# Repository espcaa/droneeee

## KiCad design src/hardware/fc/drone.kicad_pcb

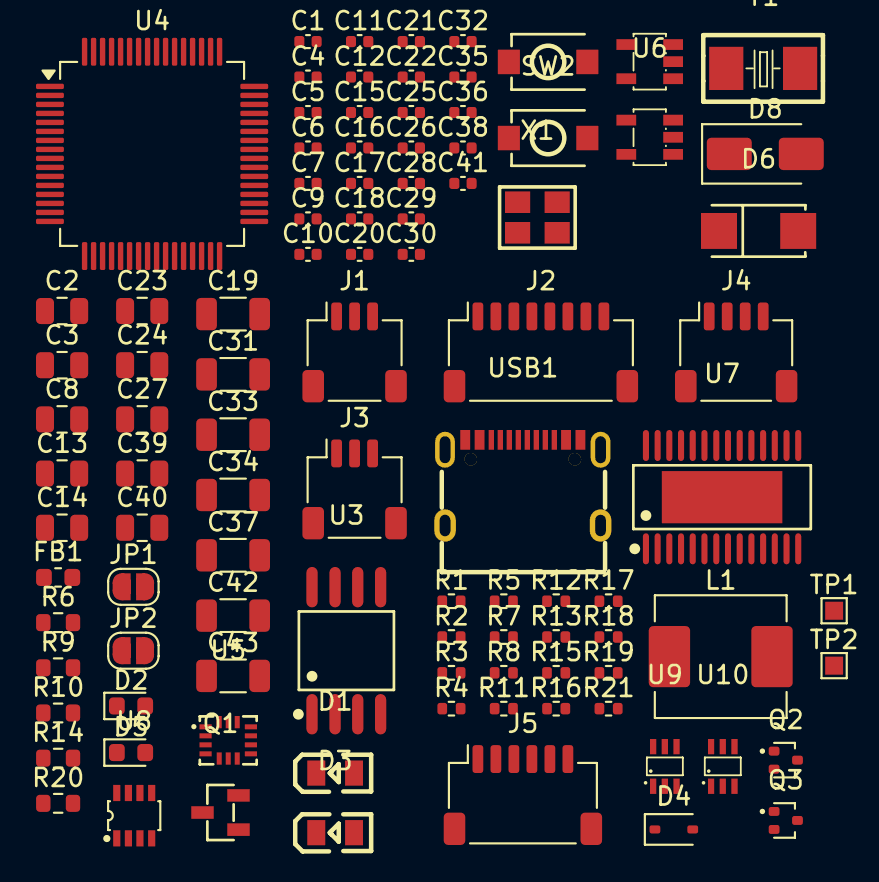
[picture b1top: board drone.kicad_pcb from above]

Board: 2 copper layers, 99 parts (0 on the bottom side), 73 nets, no tracks yet.

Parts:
C1, C4, C5, C6, C7, C11, C12, C15, C16, C17, C18, C20, C21, C22, C25, C26, C28, C29, C30, C32, C38, C41: 100nf; C_0402_1005Metric
C2, C3, C27: 2.2uf; C_0805_2012Metric
C8, C13, C14, C23, C24, C39, C40: 1uf; C_0805_2012Metric
C9, C10: 22pf; C_0402_1005Metric
C19, C31, C33, C34, C37, C42, C43: 22uf; C_1206_3216Metric
C35, C36: 33pf; C_0402_1005Metric
D1: C2297; LED0805-R-RD
D2, D5: LED; LED_0603_1608Metric
D3: C2296; LED0805-R-RD
D4: D_Schottky; D_SOD-323
D6: D_Schottky; SMA_L4.3-W2.6-LS5.2-RD
D8: SMAJ30A; D_SMA
FB1: FerriteBead; L_0603_1608Metric
J1, J3: Conn_01x03; JST_SH_SM03B-SRSS-TB_1x03-1MP_P1.00mm_Horizontal
J2: Conn_01x08; JST_SH_SM08B-SRSS-TB_1x08-1MP_P1.00mm_Horizontal
J4: Conn_01x04; JST_SH_SM04B-SRSS-TB_1x04-1MP_P1.00mm_Horizontal
J5: Conn_01x06; JST_SH_SM06B-SRSS-TB_1x06-1MP_P1.00mm_Horizontal
JP1, JP2: Jumper_2_Open; SolderJumper-2_P1.3mm_Open_RoundedPad1.0x1.5mm
L1: 1OuH; L_KOHERelec_MDA7030
Q1: AO3400A; SOT-23-3_L2.9-W1.3-P1.90-LS2.4-BR
Q2, Q3: NPN; SOT-416
R1, R2, R3, R4, R13, R17: 10k; R_0402_1005Metric
R5: 20; R_0402_1005Metric
R6: 7.68k; R_0603_1608Metric
R7: 51k; R_0402_1005Metric
R8: 41.2k; R_0402_1005Metric
R9: 1k; R_0603_1608Metric
R10, R14: 75; R_0603_1608Metric
R11, R18, R19, R21: 1k; R_0402_1005Metric
R12: 100k; R_0402_1005Metric
R15, R16: 5.1k; R_0402_1005Metric
R20: 150k; R_0603_1608Metric
SW1, SW2: SW_Push; SW-SMD_L3.9-W3.0-P4.45
TP1: BUZZER+; TestPoint_Pad_1.0x1.0mm
TP2: BUZZER-; TestPoint_Pad_1.0x1.0mm
U2: TLV75533PDBVR; SOT-23-5_L3.0-W1.7-P0.95-LS2.8-BR
U3: W25Q128JVSIQTR; SOIC-8_L5.3-W5.3-P1.27-LS8.0-BL
U4: STM32F405RGTx; LQFP-64_10x10mm_P0.5mm
U5: ICM-42688-P; LGA-14_L3.0-W2.5-P0.50-TL
U6: LP5907MFX-3.3/NOPB; SOT-23-5_L3.0-W1.7-P0.95-LS2.8-BR
U7: AT7456E; TSSOP-28_L9.7-W4.4-P0.65-LS6.4-BL-EP-2
U8: MP4420HGJ-Z; TSOT-23-8_L2.9-W1.6-P0.65-LS2.8-BL
U9, U10: LM66100DCKR; SC-70-6_L2.0-W1.3-P0.65-LS2.1-BL
USB1: TYPE-C 16PIN 2MD(073); USB-C-SMD_TYPE-C-6PIN-2MD-073
X1: XL2EL89CSI-111YLC-27M; CRYSTAL-SMD_4P-L3.2-W2.5-BL_SIT8008BI
Y1: C115962; CRYSTAL-SMD_L5.0-W3.2

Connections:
+5V: C14.1, C16.2, C23.2, C38.1, C41.1, D4.1 (K), J3.1, R3.1, R3.2, R4.1, R11.1, R18.1, TP1.1, U2.1 (IN), U2.3 (EN), U6.1 (IN), U6.3 (EN), U9.5 (ST), U9.6 (VOUT), U10.3 (~CE), U10.6 (VOUT)
BAT_CURR: C22.2, J2.3 (Current), U4.24 (PC4)
BAT_POWER: D6.2 (A), J2.1 (Power), R12.2
BAT_VOLTAGE: C21.1, R12.1, R13.2, U4.11 (PC3)
CAM_VID_OUT: C32.1, J3.3
DJI_RX: J5.3, U4.37 (PC6)
DJI_TX: J5.4, U4.38 (PC7)
GND: C2.1, C3.1, C7.2, C8.2, C9.2, C10.1, C11.2, C13.2, C14.2, C15.1, C16.1, C17.1, C19.1, C20.2, C21.2, C22.1, C23.1, C24.1, C25.2, C26.2, C27.2, C28.1, C29.1, C30.1, C31.1, C35.2, C36.2, C37.1, C38.2, C39.1, C40.2, C41.2, C42.1, C43.1, D1.1 (K), D3.1 (K), D8.2 (A2), J1.2, J2.2 (Ground), J3.2, J4.3, J5.2, J5.5, Q1.2 (S), Q2.3 (E), Q3.3 (E), R1.1, R6.2, R10.1, R13.1, R15.2, R16.1, SW2.1, U2.2 (GND), U3.4 (GND), U4.12 (VSSA), U4.18 (VSS), U4.63 (VSS), U5.2 (RESV), U5.3 (RESV), U5.6 (GND), U5.7 (RESV), U5.9 (INT2/FSYNC/CLKIN), U5.10 (RESV), U5.11 (RESV), U6.2 (GND), U7.4 (DGND), U7.20 (AGND), U7.23 (PGND), U7.29 (EP), U8.4 (GND), U9.2 (GND), U9.3 (~CE), U10.2 (GND), USB1.1 (GND), USB1.12 (GND), USB1.13 (SHELL), USB1.14 (SHELL), X1.2 (GND), X1.4 (GND)
LIPO_5V: C19.2, C37.2, C40.1, L1.2, R8.1, U10.1 (VIN)
MOTOR_1: J2.5 (Motor_1), U4.14 (PA0)
MOTOR_2: J2.6 (Motor_2), U4.15 (PA1)
MOTOR_3: J2.7 (Motor_3), U4.16 (PA2)
MOTOR_4: J2.8 (Motor_4), U4.17 (PA3)
unnamed: C18.2, R5.2
unnamed: C33.2, C34.2, R14.2
unnamed: D1.2 (A), R21.1
unnamed: D2.2 (A), R11.2
unnamed: D2.1 (K), Q2.1 (C)
unnamed: D3.2 (A), R19.1
unnamed: D4.2 (A), Q1.3 (D), TP2.1
unnamed: D5.2 (A), R18.2
unnamed: D5.1 (K), Q3.1 (C)
unnamed: C20.1, C31.2, C42.2, C43.2, D6.1 (K), D8.1 (A1), R20.2, U8.2 (IN)
unnamed: J4.4, JP1.2 (B), JP2.2 (B)
unnamed: Q2.2 (B), R4.2
unnamed: Q3.2 (B), R17.2
unnamed: R6.1, R7.2, R8.2
unnamed: R1.2, SW1.2, U4.60 (BOOT0)
unnamed: C11.1, R2.2, SW2.2, U4.7 (NRST)
unnamed: C10.2, U4.5 (PH0), Y1.1
unnamed: C9.1, U4.6 (PH1), Y1.2
unnamed: C1.2, C4.2, C5.2, C6.2, C12.2, U4.1 (VBAT), U4.19 (VDD), U4.32 (VDD), U4.48 (VDD), U4.64 (VDD)
unnamed: C3.2, U4.31 (VCAP_1)
unnamed: C2.2, U4.47 (VCAP_2)
unnamed: C7.1, C8.1, FB1.2, U4.13 (VDDA)
unnamed: C36.1, U7.5 (CLKIN), X1.3
unnamed: C34.1, U7.25 (SAG)
unnamed: C32.2, R10.2, U7.22 (VIN)
unnamed: C33.1, U7.26 (VOUT)
unnamed: C35.1, U7.6 (XFB), X1.1
unnamed: R9.2, U7.19 (~RESET)
unnamed: R5.1, U8.5 (BST)
unnamed: R20.1, U8.6 (EN/SYNC)
unnamed: R7.1, U8.8 (FB)
unnamed: C18.1, L1.1, U8.3 (SW)
unnamed: C17.2, U8.7 (VCC)
unnamed: R17.1, U10.5 (ST)
unnamed: R15.1, USB1.4 (CC1)
unnamed: R16.2, USB1.10 (CC2)
OSD_CLK: U4.51 (PC10), U7.10 (SCLK)
OSD_CS: U4.40 (PC9), U7.8 (~CS)
OSD_SDIN: U4.53 (PC12), U7.9 (SDIN)
OSD_SDOUT: U4.52 (PC11), U7.11 (SDOUT)
OSD_VID_OUT: J4.1, R14.1
PA5: U4.21 (PA5), U5.13 (AP_SCL/AP_SCLK)
PA6: U4.22 (PA6), U5.1 (AP_SDO/AP_AD0)
PA7: U4.23 (PA7), U5.14 (AP_SDA/AP_SDIO/AP_SDI)
PA8: U4.41 (PA8), U5.12 (AP_CS)
PB0: R21.2, U4.26 (PB0)
PB1: R19.2, U4.27 (PB1)
PB12: U3.1 (~CS), U4.33 (PB12)
PB13: Q1.1 (G), U3.6 (CLK), U4.34 (PB13)
PB14: U3.2 (DO), U4.35 (PB14)
PB15: U3.5 (DI), U4.36 (PB15)
TELEMETRY: J2.4 (Telemetry), U4.54 (PD2)
USB_5V: C39.2, U9.1 (VIN), USB1.2 (VBUS), USB1.11 (VBUS)
USB_D+: U4.45 (PA12), USB1.6 (DP1), USB1.8 (DP2)
USB_D-: U4.44 (PA11), USB1.5 (DN2), USB1.7 (DN1)
VACC: C24.2, C25.1, C26.1, C27.1, U5.5 (VDDIO), U5.8 (VDD), U6.5 (OUT)
VDD: C1.1, C4.1, C5.1, C6.1, C12.1, C13.1, C15.2, C28.2, C29.2, C30.2, FB1.1, R2.1, R9.1, SW1.1, U2.5 (OUT), U3.8 (VCC), U7.3 (DVDD), U7.21 (AVDD), U7.24 (PVDD)
VTX_5V: J1.1, JP2.1 (A)
VTX_12V: J1.3, J5.1, JP1.1 (A)
VTX_TX: J4.2, U4.29 (PB10)

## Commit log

2025-12-26 first commit :pf:
2025-12-26 new routing
2025-12-30 removed annoying files
